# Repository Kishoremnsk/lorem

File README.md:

View this project on [CADLAB.io](https://cadlab.io/project/29168). 

# lorem

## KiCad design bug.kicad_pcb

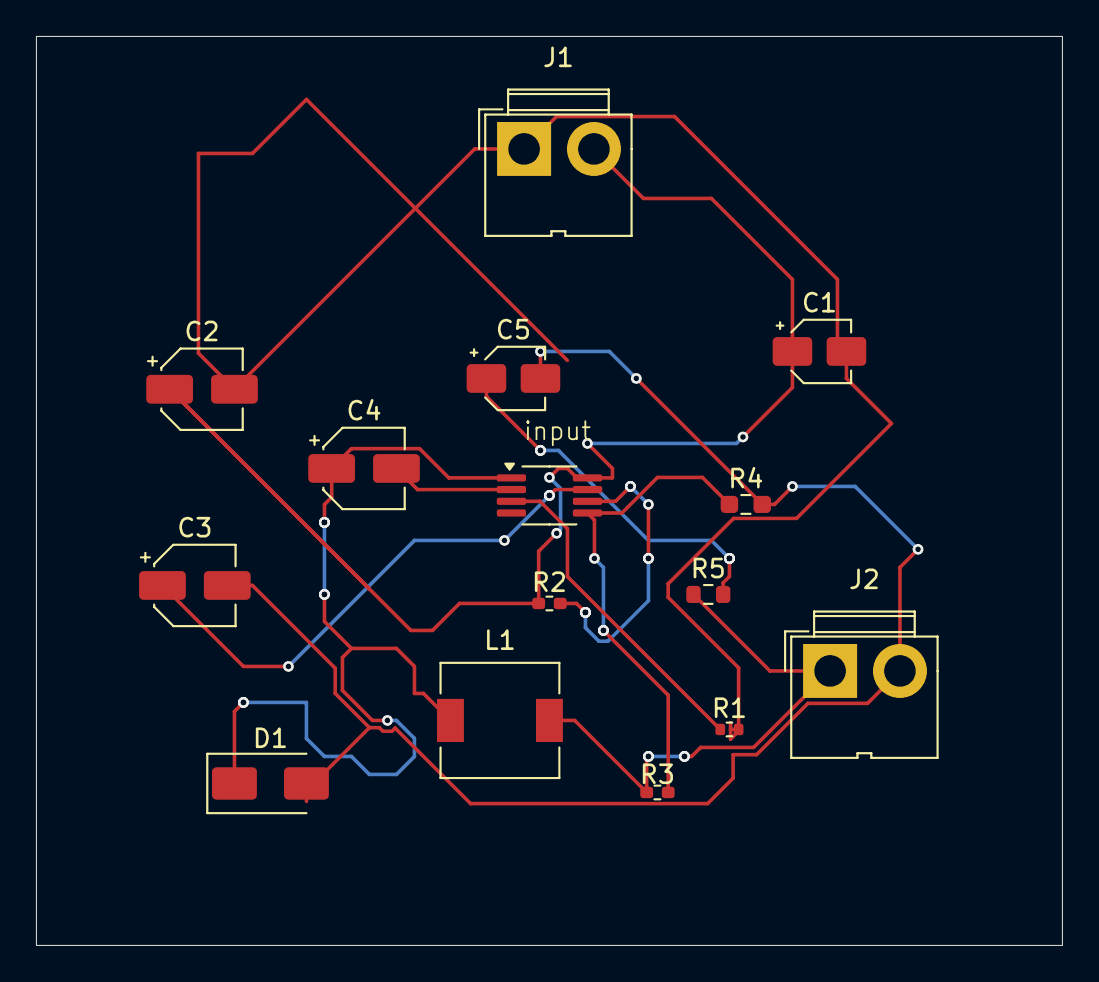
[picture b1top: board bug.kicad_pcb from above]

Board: 2 copper layers, 57.0 x 50.5 mm, 15 parts (0 on the bottom side), 11 nets.

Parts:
C1, C5: C; CP_Elec_3x5.4
C2: C; CP_Elec_4x5.3
C3: C; CP_Elec_4x4.5
C4: C; CP_Elec_4x3
D1: SS110; D_SMA
J1, J2: Screw_Terminal_01x02; JWT_A3963_1x02_P3.96mm_Vertical
L1: L; L_6.3x6.3_H3
R1: R_US; R_0402_1005Metric
R2, R3: R_US; R_0402_1005Metric_Pad0.72x0.64mm_HandSolder
R4: R_US; R_0603_1608Metric_Pad0.98x0.95mm_HandSolder
R5: R_US; R_0603_1608Metric
U1: LM5007MM; MSOP-8_3x3mm_P0.65mm

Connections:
/bst: C4.2, U1.2 (BST)
/fb: R3.2, R4.1, U1.5 (FB)
/h: R2.2, U1.6 (RON/SD)
/rcl: R1.1, U1.3 (RCL)
/sw: C4.1, D1.1 (K), L1.1, U1.1 (SW)
/vcc: C3.1, U1.7 (VCC)
/vin: C1.1, C2.1, J1.2, R2.1, U1.8 (VIN)
unnamed: C5.1, R5.2
unnamed: C3.2, C5.2, D1.2 (A), J2.2, R4.2
unnamed: C1.2, C2.2, J1.1, R1.2
unnamed: J2.1, L1.2, R3.1, R5.1

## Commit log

2025-04-04 Backlink to CADLAB.io has been added.
